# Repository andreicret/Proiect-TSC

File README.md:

# TSC OpenBook Reader - Alexandru-Andrei CRET

## Project Content

+ **Schematic & PCB Design** → Circuit design files (.sch, .brd)

+ **Manufacturing Files** → Gerber files, Bill of Materials (BOM), and Pick & Place files.

+ **3D Model & Mechanical Design** → Complete 3D assembly of the device, including PCB, battery, display, and enclosure.

+ **Renders & Images** → Visual representations of the final device and PCB layout.

+ **Documentation** → In-depth explanation of hardware architecture, component connections, and design choices.

## Device Diagram

## Hardware Modules and Components

### ESP32-C6-WROOM-1-N8  (main microcontroller)
- **Key Features:** WiFi 6, Bluetooth 5 LE, RISC-V core
- **Operating Voltage:** 3.3V
- **Communication Interfaces:** SPI, I2C, UART, GPIO

### SD Card Module
- **Interface:** SPI
- **Pin Connections:**
  - `SS_SD` → `IO5`
  - `MOSI` → `IO23`
  - `MISO` → `IO19`
  - `SCK` → `IO18`

### Buttons (User Interface)
- **Interface:** GPIO
- **Pin Connections:**
  - `BUTTON_1` → `IO0` (Used for page turning)
  - `BUTTON_2` → `IO1` (Used for accessing menu options)

### E-Ink Display
- **Interface:** SPI
- **Pin Connections:**
  - `EPD_CS` → `IO15`
  - `EPD_DC` → `IO13`
  - `EPD_RST` → `IO12`
  - `EPD_BUSY` → `IO14`
  - `MOSI`, `SCK` shared with SD card module

### Voltage Regulator (LDO)
- **Purpose:** Converts 5V to 3.3V for powering the ESP32 and other peripherals

### Charging IC (TP4056)
- **Operating Voltage:** 5V via USB-C
- **Function:** Li-Po battery charging and protection

### USB Interface (USB-C Connector)
- **Functionality:** Power and data connection for the device
- **Protection:** ESD protection via TVS diodes

### Li-Po Battery
- **Type:** 3.7V Li-Po
- **Capacity:** 2000mAh

## Communication Interfaces

| **Interface** | **Connected Components** | **ESP32-C6 Pins**                         |
|---------------|--------------------------|-------------------------------------------|
| SPI           | E-Ink Display, SD Card   | `MOSI` (`IO23`), `MISO` (`IO19`), `SCK` (`IO18`) |
| I2C           | (Optional for sensors)   | `SDA` (`IO21`), `SCL` (`IO22`)           |
| GPIO          | Buttons, reset           | `IO0`, `IO1`                             |
| USB           | Power and Data (USB-C)   | `USB_D+` (`IO14`), `USB_D-` (`IO13`)     |

## Estimated Power Consumption

| Component             | Average Consumption (mA) |
| :--------------------- | :----------------------- |
| **Typical Total**      | **150-250 mA**          |
| E-Paper (in refresh)   | 20-50 mA               |
| SD Card                | 30-100 mA              |
| DS3231 RTC             | 0.2 mA                 |
| BME688                 | 0.8 mA                 |
| ESP32-C6 (WiFi active) | 80-160 mA              |
| External Flash         | 10-20 mA               |
| ESP32-C6 (idle)        | 10 mA                  |

## Bill of Materials (BOM)

| Component Name                                      | Link                | Datasheet                        |
|--------------------------------------------------|-----------------------------------|-----------------------------------|
| BD5229G-TR                                       | [Component Search Engine](https://componentsearchengine.com/part-view/BD5229G-TR/ROHM%20Semiconductor)         | [Datasheet](https://datasheet.datasheetarchive.com/originals/distributors/Datasheets_SAMA/f2b9741ef86007909f138d561a359946.pdf)     |
| ESP32 WROVER 0805 Capacitor                      | [Mouser](https://ro.mouser.com/ProductDetail/KYOCERA-AVX/SD0805S020S1R0?qs=jCA%252BPfw4LHbpkAoSnwrdjw%3D%3D)         | [Datasheet](https://ro.mouser.com/datasheet/2/40/schottky-3165252.pdf)     |
| ESP32 WROVER MCP73831 Power Management           | [Mouser](https://eu.mouser.com/ProductDetail/Microchip-Technology/MCP73831T-2ACI-OT?qs=yUQqVecv4qvbBQBGbHx0Mw%3D%3D)         | [Datasheet](https://eu.mouser.com/datasheet/2/268/MCP73831_Family_Data_Sheet_DS20001984H-3441711.pdf)     |
| PGB1010603MR Inductor                            | [SnapMagic](https://www.snapeda.com/parts/PGB1010603MR/Littelfuse/view-part/?ref=eda)         | [Datasheet](https://www.snapeda.com/parts/PGB1010603MR/Littelfuse%20Inc./datasheet/)     |
| USBLC6-2SC6Y USB Surge Protection                | [SnapMagic](https://www.snapeda.com/parts/USBLC6-2SC6Y/STMicroelectronics/view-part/?ref=eda)        | [Datasheet](https://www.snapeda.com/parts/USBLC6-2SC6Y/STMicroelectronics/datasheet/)     |
| CPH3225A                                         | [SnapMagic](https://www.snapeda.com/parts/CPH3225A/Seiko+Instruments/view-part/?ref=eda)         | [Datasheet](https://www.snapeda.com/parts/CPH3225A/Seiko%20Instruments/datasheet/)     |
| Capacitor 0402                                   | [Component Search Engine](https://componentsearchengine.com/part-view/CC0402MRX5R5BB106/YAGEO)         | [Datasheet](https://componentsearchengine.com/Datasheets/2/CC0402MRX5R5BB106.pdf)     |
| MAX17048G+T10 Battery Fuel Gauge                 | [SnapMagic](https://www.snapeda.com/parts/MAX17048G+T10/Analog+Devices/view-part/?ref=eda)         | [Datasheet](https://www.snapeda.com/parts/MAX17048G+T10/Analog%20Devices/datasheet/)     |
| USB4110-GF-A USB Hub                             | [Component Search Engine](https://componentsearchengine.com/part-view/USB4110-GF-A/GCT%20(GLOBAL%20CONNECTOR%20TECHNOLOGY))         | [Datasheet](https://gct.co/files/drawings/usb4110.pdf)     |
| ESP32-C6 WROOM-1-N8                              | [SnapMagic](https://www.snapeda.com/parts/ESP32-C6-WROOM-1-N8/Espressif+Systems/view-part/?ref=eda)         | [Datasheet](https://www.snapeda.com/parts/ESP32-C6-WROOM-1-N8/Espressif%20Systems/datasheet/)     |
| ESP32 WROVER BME680 Sensor                       | [SnapMagic](https://www.snapeda.com/parts/BME680/Bosch/view-part/?welcome=home)        | [Datasheet](https://www.snapeda.com/parts/BME680/Bosch%20Sensortec/datasheet/)     |
| SJ                                               | [GrabCad](https://grabcad.com/library/solder-jumpers-1)         | [Datasheet](https://www.youtube.com/watch?v=dQw4w9WgXcQ)     |
| RCL CPOL 3528                                    | [SnapMagic](https://www.snapeda.com/parts/TAJB475K025RNJ/AVX/view-part/?ref=dk&t=capacitor%203528&con_ref=None)        | [Datasheet](https://s3.amazonaws.com/snapeda/datasheet/TAJB475K025RNJ_AVX.pdf)     |
| ESP32C6 Varistor 1812                            | [Mouser](https://ro.mouser.com/ProductDetail/EPCOS-TDK/B72520T0350K062?qs=dEfas%2FXlABIszF52uu7vrg%3D%3D)        | [Datasheet](https://www.tdk-electronics.tdk.com/inf/75/db/CTVS_14/Surge_protection_series.pdf)     |
| LED Chip 0603                                    | [SnapMagic](https://www.snapeda.com/parts/KP-1608SURCK/Kingbright/view-part/?ref=search&t=LED%200603)        | [Datasheet](https://www.snapeda.com/parts/KP-1608SURCK/Kingbright/datasheet/)     |
| DS3231SN RTC                                     | [SnapMagic](https://www.snapeda.com/parts/DS3231SN%23/Analog+Devices/view-part/?ref=eda)        | [Datasheet](https://www.snapeda.com/parts/DS3231SN%23/Analog%20Devices/datasheet/)     |
| TPTP20R                                          | [Comet](https://easyeda.com/component/7524403feb2642ac9f9f26dfb93ceacf)         | [Datasheet](https://easyeda.com/component/7524403feb2642ac9f9f26dfb93ceacf)     |
| FH34SRJ-24S-0.5SH Connector                      | [Component Search Engine](https://componentsearchengine.com/part-view/FH34SRJ-24S-0.5SH(99)/Hirose)        | [Datasheet](https://www.hirose.com/en/product/document?clcode=CL0580-1255-6-99&productname=FH34SRJ-24S-0.5SH(99)&series=FH34SRJ&documenttype=2DDrawing&lang=en&documentid=0000990903)     |
| QWIIC Connector                                  | [Mouser](https://eu.mouser.com/ProductDetail/Adafruit/4208?qs=PzGy0jfpSMtbScLbr0L5dw%3D%3D)        | [Datasheet](https://www.youtube.com/watch?v=dQw4w9WgXcQ)     |
| MBR0530 Schottky Diode                           | [SnapMagic](https://www.snapeda.com/parts/MBR0530/Onsemi/view-part/?ref=eda)        | [Datasheet](https://www.snapeda.com/parts/MBR0530/ON%20Semiconductor/datasheet/)     |
| XC6220A331MR-G Voltage Regulator                 | [Component Search Engine](https://componentsearchengine.com/part-view/XC6220A331MR-G/Torex)        | [Datasheet](https://product.torexsemi.com/system/files/series/xc6220.pdf)     |
| SI1308EDL-T1-GE3 MOSFET                          | [SnapMagic](https://www.snapeda.com/parts/SI1308EDL-T1-GE3/Vishay+Siliconix/view-part/?ref=eda)        | [Datasheet](https://www.youtube.com/watch?v=dQw4w9WgXcQ)     |
| 112A-TAAR-R03                                    | [Comet](https://store.comet.srl.ro/Catalogue/Product/43497/)         | [Datasheet](https://store.comet.bg/download-file.php?id=27596)     |
| ESP32 WROVER P-Channel MOSFET                    | [Component Search Engine](https://componentsearchengine.com/part-view/DMG2305UX-7/Diodes%20Incorporated)         | [Datasheet](https://www.diodes.com//assets/Datasheets/DMG2305UX.pdf)     |

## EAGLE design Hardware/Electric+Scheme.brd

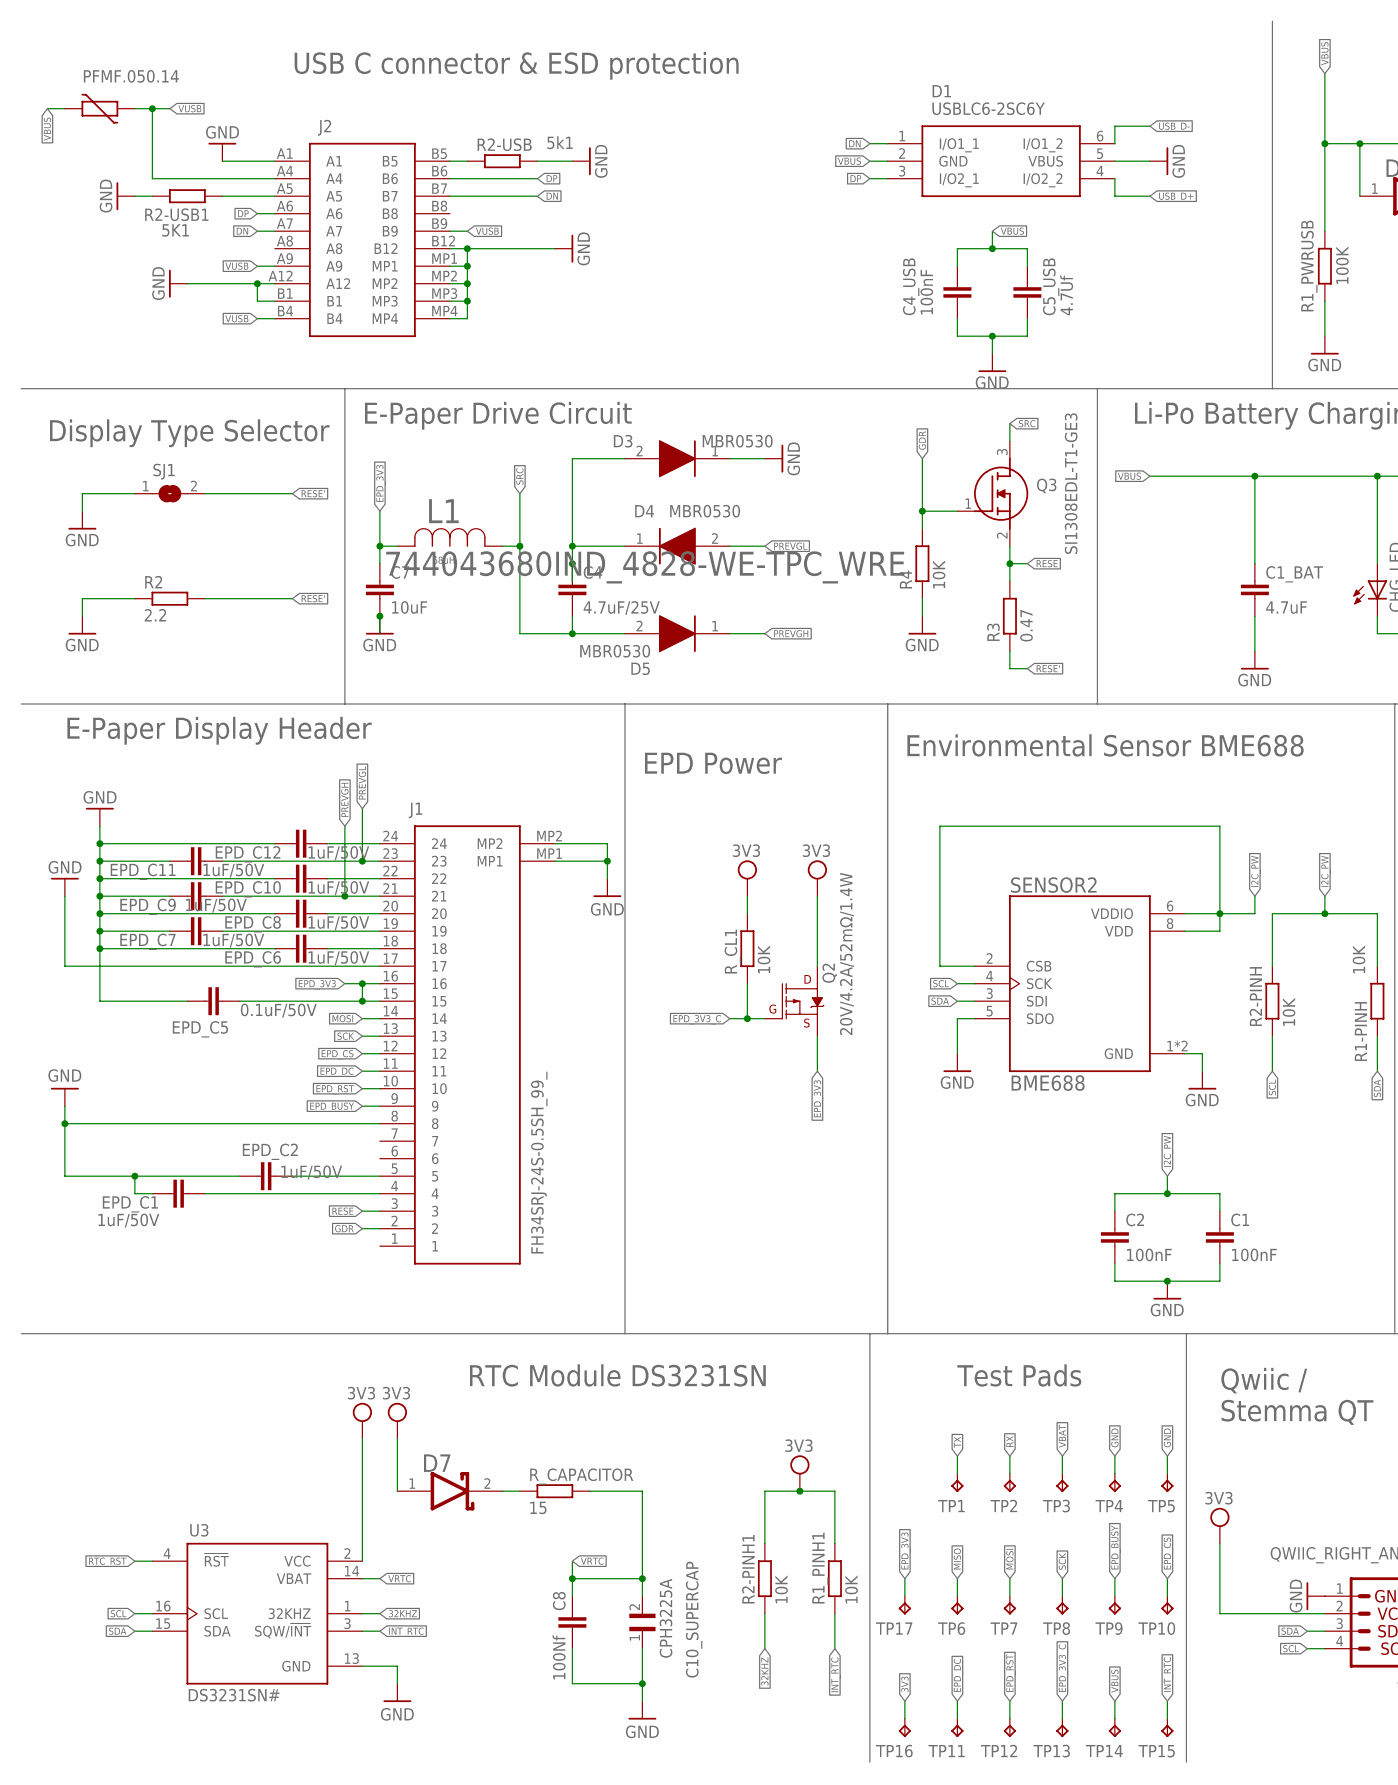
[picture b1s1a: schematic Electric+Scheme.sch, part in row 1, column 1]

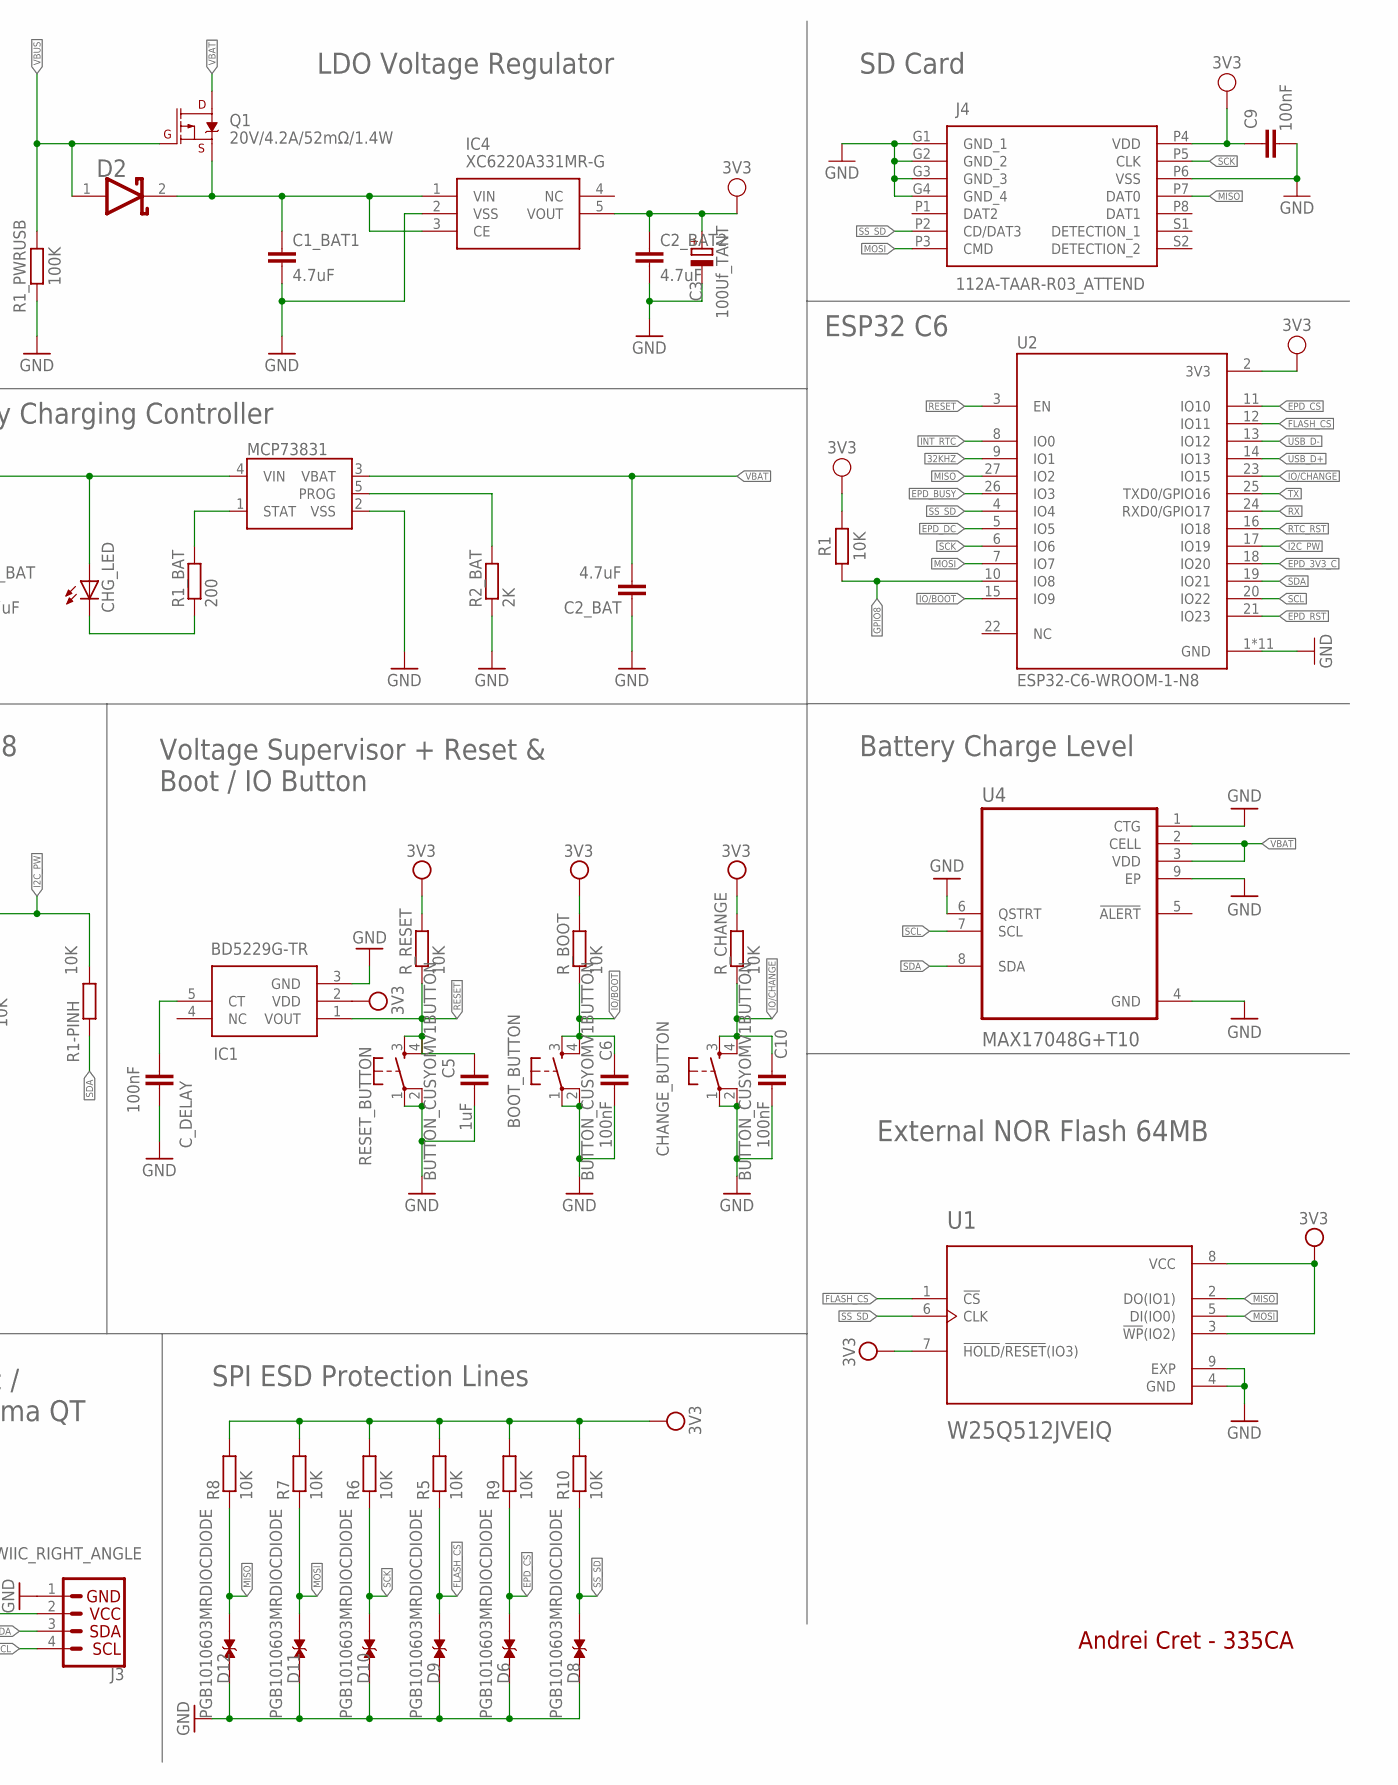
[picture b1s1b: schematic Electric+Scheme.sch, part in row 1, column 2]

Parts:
BOOT_BUTTON: BUTTON_CUSYOMV1BUTTON; MYBUTTON
C1, C2, C4_USB, C6, C10: 100nF; EAGLE-LTSPICE_C0402
C1_BAT, C1_BAT1, C2_BAT, C2_BAT2: 4.7uF; EAGLE-LTSPICE_C0402
C3: 100Uf_TANT; CAPMP3216X180N
C4: 4.7uF/25V; EAGLE-LTSPICE_C0402
C5: 1uF; EAGLE-LTSPICE_C0402
C5_USB: 4.7Uf; EAGLE-LTSPICE_C0402
C7: 10uF; EAGLE-LTSPICE_C0402
C8: 100Nf; ESP32_WROVER_EAGLE-LTSPICE_C0402
C9: 100nF; CAPC1005X60
C10_SUPERCAP: CPH3225A; CAPCP3225X100N
CHANGE_BUTTON: BUTTON_CUSYOMV1BUTTON; MYBUTTON
CHG_LED: RED; ADAFRUIT_CHIP-LED0603
C_DELAY: 100nF; EAGLE-LTSPICE_C0402
D1: USBLC6-2SC6Y; SOT95P280X145-6N
D2, D7: ESP32_WROVER_AVX---SD0805S020S1R0_AVX_SD0805S020S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; ESP32_WROVER_AVX---SD0805S020S1R0_AVX_SD0805S020S1R0_0
D3, D4, D5: MBR0530; SOD3716X135N
D6, D8, D9, D10, D11, D12: PGB1010603MRDIOCDIODE; DIOC1608X36N
EPD_C1, EPD_C2: 1uF/50V; ESP32_WROVER_EAGLE-LTSPICE_C0402
EPD_C5: 0.1uF/50V; EAGLE-LTSPICE_C0402
EPD_C6, EPD_C7, EPD_C8, EPD_C9, EPD_C10, EPD_C11, EPD_C12: 1uF/50V; EAGLE-LTSPICE_C0402
IC1: BD5229G-TR; SOT95P280X125-5N
IC4: XC6220A331MR-G; SOT95P280X120-5N
J1: FH34SRJ-24S-0.5SH_99_; FH34SRJ24S05SH99
J2: SAMACSYS_PARTS_USB4110-GF-A; SAMACSYS_PARTS_USB4110GFA
J3: QWIIC_RIGHT_ANGLE; JST04_1MM_RA
J4: 112A-TAAR-R03_ATTEND; 112ATAARR03ATTEND
L1: 744043680IND_4828-WE-TPC_WRE; IND_4828-WE-TPC_WRE
MCP73831: ESP32_WROVER_SPARKFUN-IC-POWER_MCP73831; ESP32_WROVER_SPARKFUN-IC-POWER_SOT23-5
PFMF.050.14: ESP32C6_VARISTORCN1812; ESP32C6_VARISTOR_CT/CN1812
Q1, Q2: 20V/4.2A/52mΩ/1.4W; ESP32_WROVER_SPARKFUN-DISCRETESEMI_SOT23-3
Q3: SI1308EDL-T1-GE3; SOT65P210X110-3N
R1: 10K; RESC1005X40
R1-PINH, R1_PINH1, R2-PINH, R2-PINH1, R4, R5, R6, R7, R8, R9, R10: 10K; ESP32_WROVER_EAGLE-LTSPICE_R0402
R1_BAT: 200; ESP32_WROVER_EAGLE-LTSPICE_R0402
R1_PWRUSB: 100K; RESC1005X40
R2: 2.2; ESP32_WROVER_EAGLE-LTSPICE_R0402
R2-USB: 5k1; ESP32_WROVER_EAGLE-LTSPICE_R0402
R2-USB1: 5K1; ESP32_WROVER_EAGLE-LTSPICE_R0402
R2_BAT: 2K; ESP32_WROVER_EAGLE-LTSPICE_R0402
R3: 0.47; ESP32_WROVER_EAGLE-LTSPICE_R0402
RESET_BUTTON: BUTTON_CUSYOMV1BUTTON; MYBUTTON
R_BOOT: 10K; ESP32_WROVER_EAGLE-LTSPICE_R0402
R_CAPACITOR: 15; ESP32_WROVER_EAGLE-LTSPICE_R0402
R_CHANGE: 10K; ESP32_WROVER_EAGLE-LTSPICE_R0402
R_CL1: 10K; ESP32_WROVER_EAGLE-LTSPICE_R0402
R_RESET: 10K; ESP32_WROVER_EAGLE-LTSPICE_R0402
SENSOR2: BME688; ESP32_WROVER_BME680_PSON80P300X300X100-8N
SJ1: SOLDERJUMPER; SJ
TP1, TP2, TP3, TP4, TP5, TP6, TP7, TP8, TP9, TP10, TP11, TP12, TP13, TP14, TP15, TP16, TP17: TP; TP20R
U1: W25Q512JVEIQ; SON127P600X800X80-9N
U2: ESP32-C6-WROOM-1-N8; XCVR_ESP32-C6-WROOM-1-N8
U3: DS3231SN#; SOIC127P1032X265-16N
U4: MAX17048G+T10; SON50P200X200X80-9N

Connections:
3V3: C2_BAT2.1, C3.1 (+), C9.2, D7.1 (ANODE), IC1.2 (VDD), IC4.5 (VOUT), J3.2, J4.P4 (VDD), Q2.3 (D), R1.2, R1_PINH1.2, R2-PINH1.2, R5.2, R6.2, R7.2, R8.2, R9.2, R10.2, R_BOOT.2, R_CHANGE.2, R_CL1.2, R_RESET.2, TP16.TP, U1.3 (!WP!(IO2)), U1.7 (!HOLD!/!RESET!(IO3)), U1.8 (VCC), U2.2 (3V3), U3.2 (VCC)
32KHZ: R2-PINH1.1, U2.9 (IO1), U3.1 (32KHZ)
DN: D1.1 (I/O1_1), J2.A7, J2.B7
DP: D1.3 (I/O2_1), J2.A6, J2.B6
EPD_3V3: C7.1, EPD_C5.2, J1.15, J1.16, L1.2, Q2.2 (S), TP17.TP
EPD_3V3_C: Q2.1 (G), R_CL1.1, TP13.TP, U2.18 (IO20)
EPD_BUSY: J1.9, TP9.TP, U2.26 (IO3)
EPD_CS: D6.2, J1.12, R9.1, TP10.TP, U2.11 (IO10)
EPD_DC: J1.11, TP11.TP, U2.5 (IO5)
EPD_RST: J1.10, TP12.TP, U2.21 (IO23)
FLASH_CS: D9.2, R5.1, U1.1 (!CS), U2.12 (IO11)
GDR: J1.2, Q3.1 (G), R4.2
GND: BOOT_BUTTON.1, BOOT_BUTTON.2, C1.2, C1_BAT.2, C1_BAT1.2, C2.2, C2_BAT.1, C2_BAT2.2, C3.2 (-), C4_USB.2, C5.2, C5_USB.2, C6.2, C7.2, C8.2, C9.1, C10.2, C10_SUPERCAP.1, CHANGE_BUTTON.1, CHANGE_BUTTON.2, C_DELAY.2, D1.5 (VBUS), D3.1 (K), D6.1, D8.1, D9.1, D10.1, D11.1, D12.1, EPD_C1.1, EPD_C2.1, EPD_C5.1, EPD_C6.1, EPD_C7.1, EPD_C8.1, EPD_C9.1, EPD_C10.1, EPD_C11.1, EPD_C12.1, IC1.3 (GND), IC4.2 (VSS), J1.8, J1.17, J1.MP1, J1.MP2, J2.A1, J2.A12, J2.B1, J2.B12, J2.MP1, J2.MP2, J2.MP3, J2.MP4, J3.1, J4.G1 (GND_1), J4.G2 (GND_2), J4.G3 (GND_3), J4.G4 (GND_4), J4.P6 (VSS), MCP73831.2 (VSS), R1_PWRUSB.1, R2.1, R2-USB.2, R2-USB1.1, R2_BAT.1, R4.1, RESET_BUTTON.1, RESET_BUTTON.2, SENSOR2.1 (GND), SENSOR2.5 (SDO), SENSOR2.7 (GND), SJ1.1, TP4.TP, TP5.TP, U1.4 (GND), U1.9 (EXP), U2.1 (GND), U2.28 (GND), U2.29_1 (GND), U2.29_2 (GND), U2.29_3 (GND), U2.29_4 (GND), U2.29_5 (GND), U2.29_6 (GND), U2.29_7 (GND), U2.29_8 (GND), U2.29_9 (GND), U3.13 (GND), U4.1 (CTG), U4.4 (GND), U4.6 (QSTRT), U4.9 (EP)
GPIO8: R1.1, U2.10 (IO8)
I2C_PW: C1.1, C2.1, R1-PINH.2, R2-PINH.2, SENSOR2.2 (CSB), SENSOR2.6 (VDDIO), SENSOR2.8 (VDD), U2.17 (IO19)
INT_RTC: R1_PINH1.1, TP15.TP, U2.8 (IO0), U3.3 (SQW/!INT)
IO/BOOT: BOOT_BUTTON.3, BOOT_BUTTON.4, C6.1, R_BOOT.1, U2.15 (IO9)
IO/CHANGE: C10.1, CHANGE_BUTTON.3, CHANGE_BUTTON.4, R_CHANGE.1, U2.23 (IO15)
MISO: D12.2, J4.P7 (DAT0), R8.1, TP6.TP, U1.2 (DO(IO1)), U2.27 (IO2)
MOSI: D11.2, J1.14, J4.P3 (CMD), R7.1, TP7.TP, U1.5 (DI(IO0)), U2.7 (IO7)
unnamed: C1_BAT1.1, D2.2 (CATHODE), IC4.1 (VIN), IC4.3 (CE), Q1.2 (S)
unnamed: C4.1, D3.2 (A), D4.1 (K)
unnamed: J2.B5, R2-USB.1
unnamed: MCP73831.1 (STAT), R1_BAT.2
unnamed: CHG_LED.C, R1_BAT.1
unnamed: MCP73831.5 (PROG), R2_BAT.2
unnamed: D7.2 (CATHODE), R_CAPACITOR.1
unnamed: J2.A5, R2-USB1.2
unnamed: EPD_C2.2, J1.5
unnamed: EPD_C1.2, J1.4
unnamed: D8.2, R10.1
unnamed: C_DELAY.1, IC1.5 (CT)
unnamed: EPD_C12.2, J1.24
unnamed: EPD_C6.2, J1.18
unnamed: EPD_C7.2, J1.19
unnamed: EPD_C10.2, J1.22
unnamed: EPD_C8.2, J1.20
PREVGH: D5.1 (K), EPD_C9.2, J1.21
PREVGL: D4.2 (A), EPD_C11.2, J1.23
RESE: J1.3, Q3.2 (S), R3.2
RESE': R2.2, R3.1, SJ1.2
RESET: C5.1, IC1.1 (VOUT), RESET_BUTTON.3, RESET_BUTTON.4, R_RESET.1, U2.3 (EN)
RTC_RST: U2.16 (IO18), U3.4 (!RST)
RX: TP2.TP, U2.24 (RXD0/GPIO17)
SCK: D10.2, J1.13, J4.P5 (CLK), R6.1, TP8.TP, U2.6 (IO6)
SCL: J3.4, R2-PINH.1, SENSOR2.4 (SCK), U2.20 (IO22), U3.16 (SCL), U4.7 (SCL)
SDA: J3.3, R1-PINH.1, SENSOR2.3 (SDI), U2.19 (IO21), U3.15 (SDA), U4.8 (SDA)
SRC: C4.2, D5.2 (A), L1.1, Q3.3 (D)
SS_SD: J4.P2 (CD/DAT3), U1.6 (CLK), U2.4 (IO4)
TX: TP1.TP, U2.25 (TXD0/GPIO16)
USB_D+: D1.4 (I/O2_2), U2.14 (IO13)
USB_D-: D1.6 (I/O1_2), U2.13 (IO12)
VBAT: C2_BAT.2, MCP73831.3 (VBAT), Q1.3 (D), TP3.TP, U4.2 (CELL), U4.3 (VDD)
VBUS: C1_BAT.1, C4_USB.1, C5_USB.1, CHG_LED.A, D1.2 (GND), D2.1 (ANODE), MCP73831.4 (VIN), PFMF.050.14.2, Q1.1 (G), R1_PWRUSB.2, TP14.TP
VRTC: C8.1, C10_SUPERCAP.2, R_CAPACITOR.2, U3.14 (VBAT)
VUSB: J2.A4, J2.A9, J2.B4, J2.B9, PFMF.050.14.1

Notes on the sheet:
SD Card
USB C connector & ESD protection
LDO Voltage Regulator
Display Type Selector
E-Paper Drive Circuit
Li-Po Battery Charging Controller
ESP32 C6
E-Paper Display Header
EPD Power
Environmental Sensor BME688
Voltage Supervisor + Reset & Boot / IO Button
Battery Charge Level
RTC Module DS3231SN
Test Pads
Qwiic / Stemma QT
SPI ESD Protection Lines
External NOR Flash 64MB
Andrei Cret - 335CA

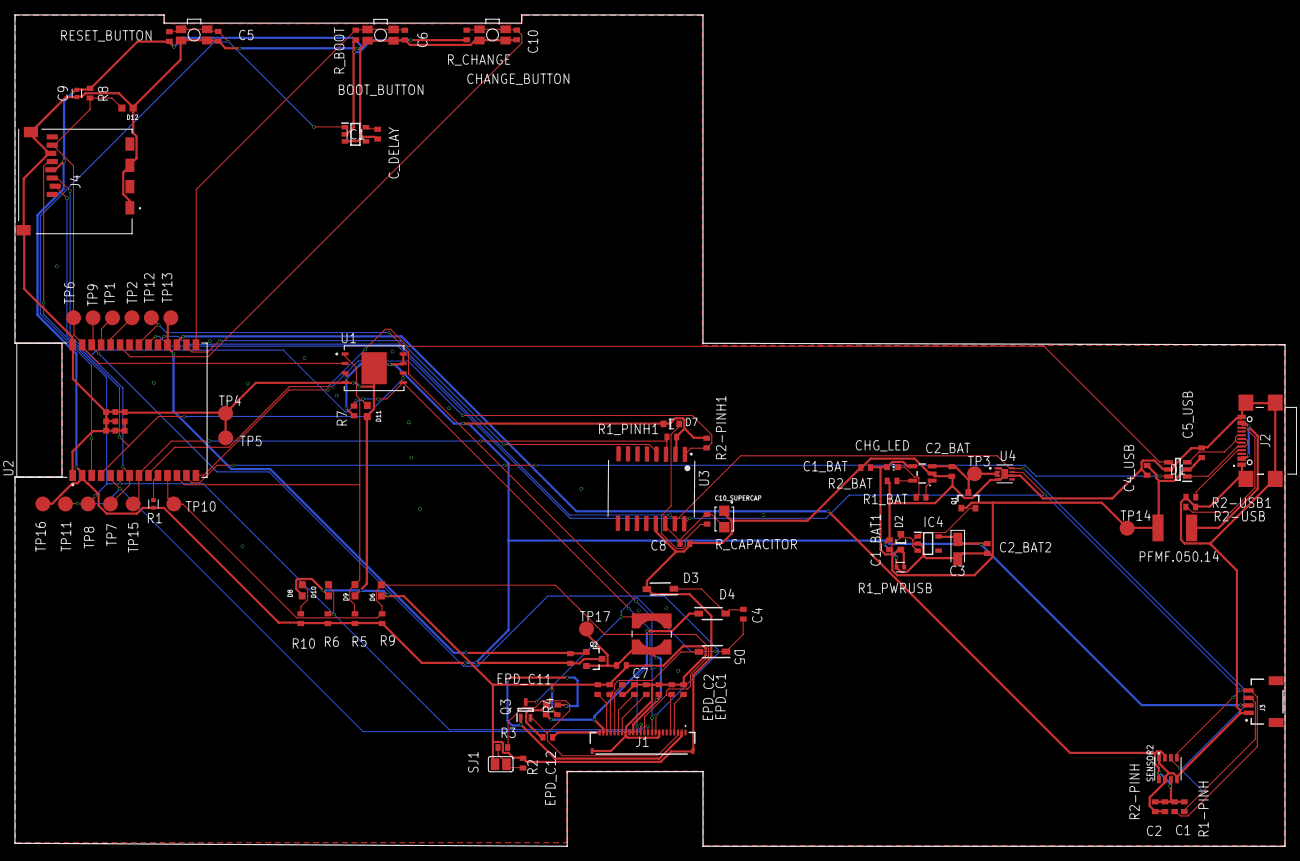
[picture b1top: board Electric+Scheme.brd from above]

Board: 2 copper layers, 170.2 x 111.4 mm, 103 parts (0 on the bottom side), 56 nets.

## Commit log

2025-04-05 Create LICENSE
2025-04-06 Create to_delete
2025-04-06 Create Images
2025-04-06 Create delete
2025-04-14 Add files via upload
    Created a new Exploded View, issue is done.
2025-04-14 Add files via upload
    Updated pcb, rerouted and moved labels.
2025-04-15 Update plan de masa.

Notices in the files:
parts and their libraries:
COPYRIGHT: Copyright (C) 2024 Ultra Librarian. All rights reserved.
